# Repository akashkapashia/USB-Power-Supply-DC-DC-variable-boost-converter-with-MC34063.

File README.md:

# USB-Power-Supply-DC-DC-variable-boost-converter-with-MC34063.
DC-DC variable boost converter with MC34063 with input as 5V from USB or power bank.

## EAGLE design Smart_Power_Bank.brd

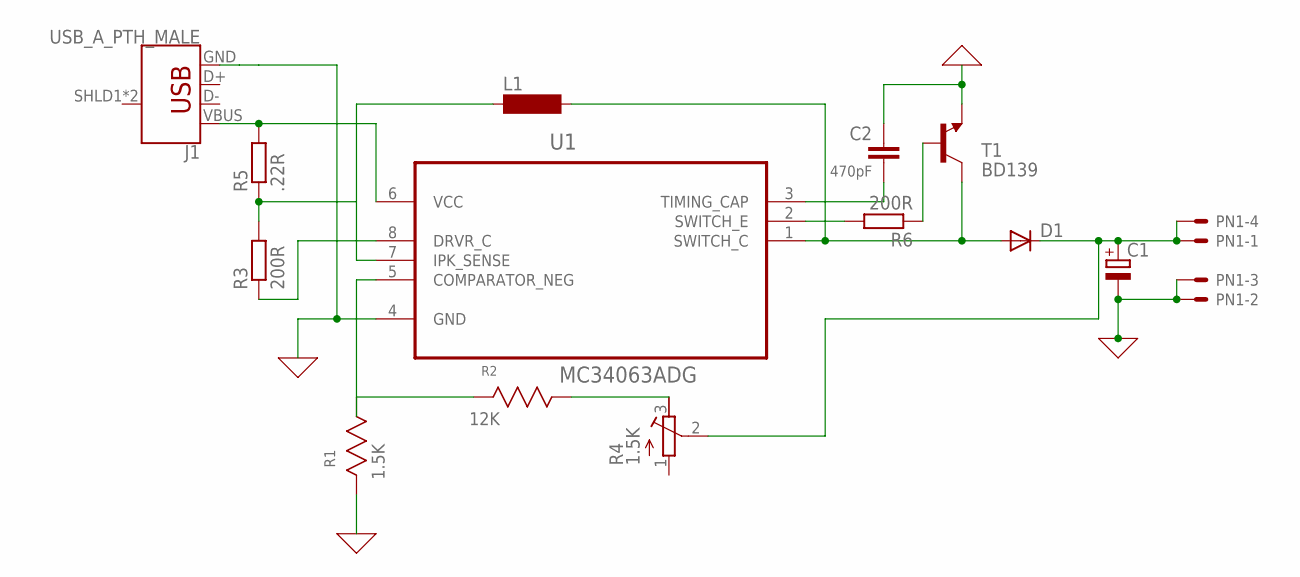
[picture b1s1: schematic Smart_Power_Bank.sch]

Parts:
C1: CPOL-EUTT2D6; TT2D6
C2: 470pF; C0805
D1: DIODE-C1702-05; C1702-05
J1: USB_A_PTH_MALE; USB-A-H
L1: BS11
PN1: 22-23-2041
R1: 1.5K; RESC2013X65N
R2: 12K; RESC2013X65N
R3, R6: 200R; R0805
R4: 1.5K; RTRIM74X
R5: .22R; 0204V
T1: BD139; TO126
U1: MC34063ADG; SOIC127P600X175-8N

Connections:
0: C1.-, C2.2, J1.GND, PN1.2, PN1.3, R1.2, T1.1 (E), U1.4 (GND)
unnamed: J1.VBUS, R5.2, U1.6 (VCC)
unnamed: D1.A, L1.2, T1.2 (C), U1.1 (SWITCH_C)
unnamed: R1.1, R2.2, U1.5 (COMPARATOR_NEG)
unnamed: R6.1, T1.3 (B)
unnamed: C1.+, D1.C, PN1.1, PN1.4, R4.2 (S)
unnamed: R2.1, R4.3 (E)
unnamed: C2.1, U1.3 (TIMING_CAP)
unnamed: R3.1, U1.8 (DRVR_C)
unnamed: L1.1, R3.2, R5.1, U1.7 (IPK_SENSE)
unnamed: R6.2, U1.2 (SWITCH_E)

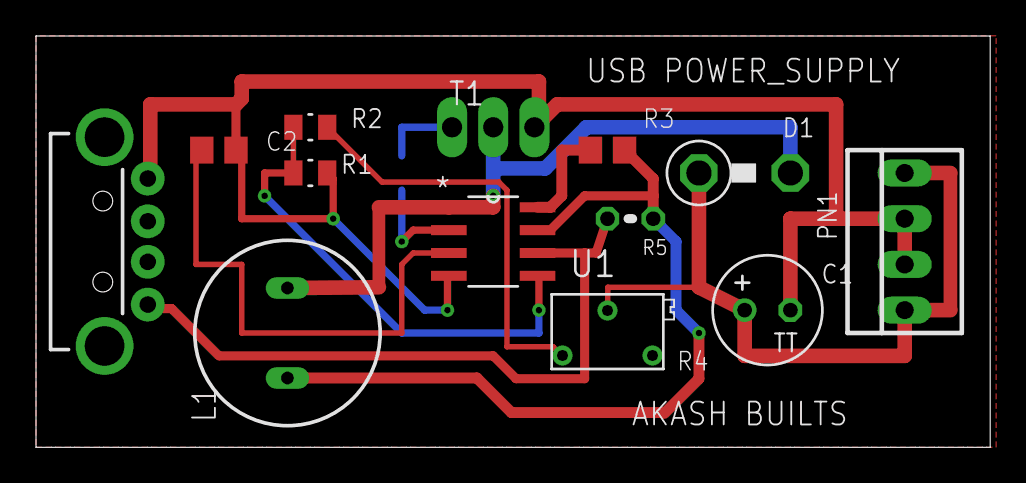
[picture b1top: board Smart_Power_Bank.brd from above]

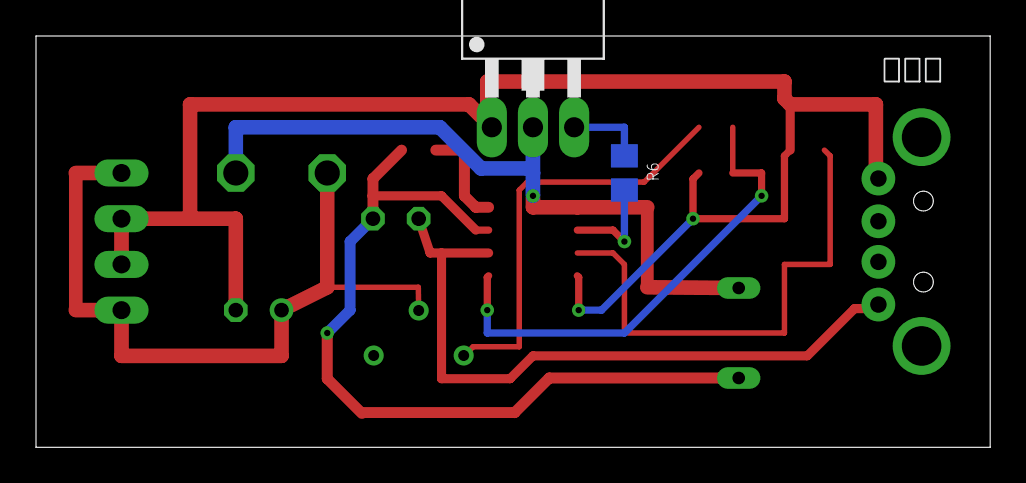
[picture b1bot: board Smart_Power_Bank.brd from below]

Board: 2 copper layers, 53.0 x 22.8 mm, 14 parts (2 on the bottom side), 11 nets.

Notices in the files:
parts and their libraries:
SparkFun-Connectors: Licensing: Creative Commons ShareAlike 4.0 International - https://creativecommons.org/licenses/by-sa/4.0
